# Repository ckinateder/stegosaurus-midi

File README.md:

# stegosaurus

Stegosaurus is an open-source MIDI controller. The controller is built around the Arduino framework and uses the MIDI protocol to communicate with a computer. It is designed to be easily configurable, with the ability to change the behavior of the controller using SysEx messages. 

TODO:
- [x] Add hardware MIDI support to the Pico
- [x] Add SysEx support to the Pico
- [ ] Web interface for programming
    - [x] Basic interaction
    - [ ] Add SysEx messages
- [ ] EEPROM module
- [ ] Pinouts
## Project Structure

This project is organized as follows:

- [`firmware/`](firmware/): main firmware code
- [`interface/`](interface/): code for the web interface

### Firmware

This project runs on the **Raspberry Pi Pico**.
To set it up in the Arduino IDE, follow [this guide](https://randomnerdtutorials.com/programming-raspberry-pi-pico-w-arduino-ide/). You will probably have to hold down the BOOTSEL button while plugging in the Pico to get it into bootloader mode for the first time. Pay attention to these upload settings:

.

Make sure the selected port matches the port that the Pico is connected to.

Required libraries:

- [EasyButton](https://github.com/evert-arias/EasyButton) (@v2.0.3)
- [Adafruit TinyUSB](https://github.com/adafruit/Adafruit_TinyUSB_Arduino) (@v3.1.4)

## Interface for Programming

See [this page](https://learn.sparkfun.com/tutorials/midi-tutorial/advanced-messages) for a good reference on MIDI messages.

The Stegosaurus will use SysEx messages to change the behavior of the controller. 

The manufacturer ID for the USB MIDI SysEx messages is `0x00 0x53 0x4D`. The `0x00` indicates that the message has a vendor ID, and the `0x53 0x4D` is the ASCII representation of "SM". This is a unique identifier for the Stegosaurus MIDI controller (I think it is unique). So, if you see a message with this ID, it is likely from the Stegosaurus. The rest of the message is the actual data.

To program the controller behavior, the interface will send a SysEx message with the manufacturer ID, followed by the command byte, and then the data. Keep in mind that the SysEx message maximum length is 128 bytes. This is using this [here](https://github.com/FortySevenEffects/arduino_midi_library/wiki/Using-custom-Settings), but I don't think that any of the messages will be even close to that length.

## MIDI Messages

The Stegosaurus will use the following MIDI messages. Keep in mind that the first 4 bytes of the message are specific to the SysEx MIDI protocol. The rest of the message is the actual data. In accordance with standard practice, every SysEx message is concluded with the SysEx end byte `0xF7`.

### Memory Layout
There are 128 presets, each with 17 slots, and 7 bytes per slot. The slots are numbered 1-16, with slot 0 reserved for metadata. The metadata for each preset is as follows:

| Byte | Description    |
|------|----------------|
| 0    | Switch type    |
| 1    | Switch values  |

The switch type is a 1-byte value that indicates the type of switch that the preset uses. Each bit from right to left indicates a switch. 0 is a momentary switch, and 1 is a latching switch. For example, `0b10000000` would mean that SWA is LATCHING and the rest are momentary.

The switch values are a 1-byte value that indicates the current state of the switches. Each bit from right to left indicates a switch. 0 is off, and 1 is on. For example, `0b10000000` would mean that SWA is on and the rest are off. This only applies to latching switches. This value is tracked so that the user can set a switch to a specific state when they enter a preset. **Note: There is not currently a way to set this data over the MIDI bus. It must be hard-coded. This will be fixed in the future.**

The rest of the slots are the actual data for the preset. Each slot is 7 bytes long. The data is as follows:

| Byte | Description    |
|------|----------------|
| 0    | Trigger        |
| 1    | Action         |
| 2    | Switch number  |
| 3    | MIDI channel   |
| 4    | Data 1         |
| 5    | Data 2         |
| 6    | Data 3         |

This can be visualized in the following diagram:

### Message Structure

The message is broken up into 2 parts: the header and the data. The header is the first 8 bytes of the message, and the data is the rest of the message.

The Message ID is a 2-byte value that is unique to each message. This is used to ensure that the message is not a duplicate. The message ID is generated by the interface and is incremented for each message. The Stegosaurus will respond with the same message ID in the response message. The message ID is ONLY ever 0 if it's unitialized. Once the maximum value is reached, it will reset to 1. The device itself will never initiate a message, so it will never have to generate a message ID. It will only respond to messages.

#### Header

| Byte | Description | Value                                                            |
|------|------------|-----------------------|
| 0 | Status byte | 0xF0 (SysEx start) |
| 1 | Vendor ID | 0x00 (Three-byte Vendor ID) |
| 2 | Vendor ID | 0x53 (Vendor ID) |
| 3 | Vendor ID | 0x4D (Vendor ID) |
| 4 | Message ID byte 1| Unique ID to ensure proper separation of messages |
| 5 | Message ID byte 2| Unique ID to ensure proper separation of messages |
| 6 | Condition* | 0, 1, or 2|
| 7 | Message type** | See table |

**\*Conditions:**

| Type | Description                | Details|
|------|----------------------------|-|
| 0    | Request                    | The interface is requesting an action from the Stegosaurus |
| 1    | ResponseOk                 | The device is responding to a request w/o error |
| 2    | ResponseError              | The device is responding to a request with an error |

**\*\*Message types:**

| Type | Description                |
|------|----------------------------|
| 0    | Write to a slot            |
| 1    | Read from a slot           |
| 2    | System parameter set       |
| 3    | System parameter get       |
| 4    | Get preset                 |

#### Message Data

The data is the rest of the message. There are 3 types of messages: write to a slot, read from a slot, and system parameter set. Each message has a different format.

#### Write to a Slot

| Byte | Description    |
|------|----------------|
| 5    | Preset to modify |
| 6    | Slot to modify |
| 7    | Trigger  |  
| 8    | Action |
| 9    | Switch number |  
| 10   | MIDI channel   |
| 11   | Data 1 |
| 12   | Data 2 |
| 13   | Data 3 |

The trigger, action, and switch number are all 1-byte values. The trigger is what will cause the action to occur. The action is the MIDI message that will be sent. The switch number is the switch that the action will be associated with, if the trigger is a type of press.

| Trigger        | Value |
|----------------|-------|
| EnterPreset    | 1     |
| ExitPreset     | 2     |
| ShortPress     | 3     |
| LongPress      | 4     |
| DoublePress    | 5     |

| Action         | Value |
|----------------|-------|
| ControlChange  | 1     |
| ProgramChange  | 2     |
| PresetUp       | 3     |
| PresetDown     | 4     |

| Switch         | Value |
|----------------|-------|
| SWA            | 0     |
| SWB            | 1     |
| SWC            | 2     |
| SWD            | 3     |

This message will write the data to the specified preset and slot in memory.

#### Read from a Slot

| Byte | Description    |
|------|----------------|
| 5    | Preset to read |
| 6    | Slot to read |

This returns the data from the specified slot in the specified preset in the same format as the write message.
Note that the preset and slot are returned in the message.

#### System Parameter Set

| Byte | Description    |
|------|----------------|
| 5    | Parameter to set |
| 6    | Value to set |

This sets a system parameter. The parameters are as follows:

| Parameter      | Value |
|----------------|-------|
| CurrentPreset  | 0     |

This message will set the specified parameter to the specified value.

#### System Parameter Get

| Byte | Description    |
|------|----------------|
| 5    | Parameter to get |

This gets a system parameter. The parameters are the same as the set message.

#### Get Preset

| Byte | Description    |
|------|----------------|
| 5    | Preset to get |

This returns the data for the specified preset. Note: this will be a long array.

### Example Messages

#### Write to a Slot
#### Read from a Slot
#### System Parameter Set
#### System Parameter Get
#### Get Preset

## Interface

This will have to use WebMIDI to communicate with the Arduino.

A good first step for this is to get a list of MIDI devices. I want to do this in React.

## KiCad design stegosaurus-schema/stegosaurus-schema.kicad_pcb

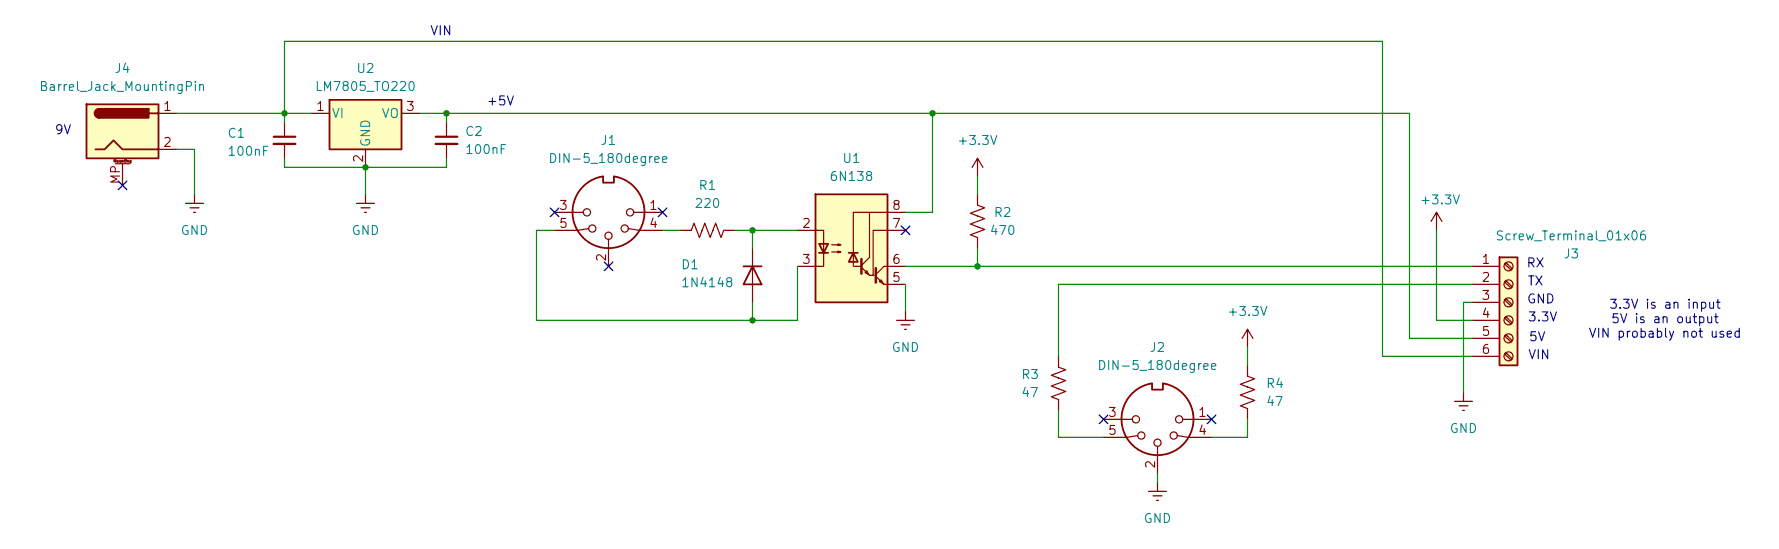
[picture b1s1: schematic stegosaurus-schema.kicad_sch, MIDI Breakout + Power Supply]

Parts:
C1, C2: 100nF; C_Disc_D3.4mm_W2.1mm_P2.50mm
D1: 1N4148; D_DO-35_SOD27_P7.62mm_Horizontal
J1, J2: DIN-5_180degree; MIDI_DIN5
J3: Screw_Terminal_01x06; TerminalBlock_bornier-6_P5.08mm
J4: Barrel_Jack_MountingPin; BarrelJack_CUI_PJ-102AH_Horizontal
R1: 220; R_Axial_DIN0204_L3.6mm_D1.6mm_P7.62mm_Horizontal
R2: 470; R_Axial_DIN0204_L3.6mm_D1.6mm_P7.62mm_Horizontal
R3, R4: 47; R_Axial_DIN0204_L3.6mm_D1.6mm_P7.62mm_Horizontal
U1: 6N138; DIP-8_W7.62mm_Socket
U2: LM7805_TO220; TO-220-3_Vertical

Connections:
+3.3V: J3.4, R2.1, R4.1
GND: C1.2, C2.2, J2.2, J3.3, J4.2, U1.5 (GND), U2.2 (GND)
unnamed: D1.2 (A), J1.5, U1.3 (C2)
unnamed: D1.1 (K), R1.2, U1.2 (C1)
unnamed: J1.4, R1.1
unnamed: J2.4, R4.2
unnamed: J2.5, R3.2
unnamed: J3.1, R2.2, U1.6 (VO2)
unnamed: J3.2, R3.1
unnamed: C2.1, J3.5, U1.8 (VCC), U2.3 (VO)
unnamed: C1.1, J3.6, J4.1, U2.1 (VI)

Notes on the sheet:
VIN
3.3V
GND
3.3V is an input 5V is an output VIN probably not used
+5V

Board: 2 copper layers, 13 parts (0 on the bottom side), 11 nets, no tracks yet.

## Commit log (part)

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2024-05-01 add submodules
2024-05-01 remove submodule
2024-05-01 add firmware dir
2024-05-01 added read
2024-05-03 microusb addition
2024-05-03 he has name
2024-05-04 sysex framework in
2024-05-06 readme updates and firmware
2024-05-06 more
2024-05-06 vendor matching
2024-05-07 progress
2024-05-12 start to use the pico
2024-05-23 start adding schematics
2024-05-31 schematics
2024-06-08 pico works on hardware
2024-06-09 more values
2024-06-11 readme fix
2024-06-16 started interface
2024-06-16 change icon
2024-06-17 readme and arduino
2024-06-17 add image
2024-06-17 add more todos
2024-06-21 pico changes
2024-06-22 load preset
2024-06-23 more handlers
2024-06-24 sample button config
2024-06-24 switch enum
2024-06-25 executeswitchaction
2024-06-25 progress - ab to change memory
2024-06-28 about to drop switch type from slots
2024-06-29 untested but compiled: states
2024-06-29 progresss, but switches aren't matching
2024-06-29 flip flop works
2024-06-29 loading latch on start
2024-06-30 slots fixed
2024-06-30 memory modification seems to be working. must cleanup
2024-06-30 change printing
2024-07-06 remove sw_offset
2024-07-09 baseline interface
2024-07-13 lots of progress
2024-07-13 saving preset works well
2024-07-13 add get slot
2024-07-13 starting to get slots
2024-07-16 prog
2024-07-20 adding checksum
2024-07-22 start adding timestamp to messages
2024-07-22 add doc
2024-07-27 starting to switch to using the message ID
2024-07-28 updated pico to use msg ids and attitudes, interface NOT updated
2024-07-28 adding condition
2024-08-27 docs update
